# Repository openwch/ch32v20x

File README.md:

# 32-bit Enhanced Low-Power RISC-V MCU – CH32V203
EN | [中文](README_zh.md)

### Overview
The CH32V203 is an industrial-grade enhanced low-power general-purpose MCU based on 32-bit RISC-V core. The CH32V203 features high performance, and supports up to 144MHz system clock frequency. The operating power consumption can be as low as 45uA/MHz. CH32V203 integrates 2-channel USB interface which supports USB Host and USB Device functions. The CH32V203 provides 1-channel CAN interface (2.0B active), 2-channel OPA, 4 UARTs, 2 IICs, 12-bit ADC, 10-channel TouchKey and other peripheral resources. Several packages such as TSSOP20, QFN28 QFN48, LQFP32 and LQFP48 are available for users.

### System Block Diagram

### Features
- Qingke V4B, up to 144MHz system clock frequency;
- Single-cycle multiplication and hardware division;
- 20KB SRAM, 64KB Flash;
- Supply voltage: 2.5V/3.3V. GPIO unit is supplied independently;
- Low-power modes: sleep/stop/standby;
- Down to 44.65uA/MHz in Run mode;
- Down to 17.90uA/MHz in Sleep mode;
- Power-on/power-down reset (POR/PDR), programmable voltage detector (PVD);
- 1 x 18-channel general DMA controllers
- 2 amplifiers;
- 10-channel 12-bit ADC, 10-channel TouchKey;
- 4 timers;
- One USB2.0 full-speed host/device interface;
- One USB2.0 full-speed device interface
- 4 UARTs;
- One CAN interface (2.0B active);
- 2 IIC interfaces, 2 SPI interfaces;
- 37 I/O ports, can be mapped to 16 external interrupts;
- CRC calculation unit, 96-bit unique ID;
- Serial 2-wire debug interface;
- Packages: TSSOP20, QFN28, QFN48, LQFP32, LQFP48;

# 32-bit Wireless RISC-V MCU – CH32V208

### Overview
The CH32V208 is a wireless MCU based on 32-bit RISC-V core, with hardware stack area and fast interrupt entry. Compared with standard RISC-V, the interrupt response speed is greatly improved. The CH32V208 is based on V4C core. The memory protection unit is added and hardware division cycle is reduced. The CH32V208 integrates 2Mbps BLE communication module, 10M Ethernet module (MAC+PHY), USB2.0 full-speed device and host/device interface, CAN controller, etc.

### System Block Diagram

### Features
- Qingke V4C processor, up to 144MHz system clock frequency;
- Single-cycle multiplication and hardware division;
- 64KB SRAM, 128KB Flash;
- Supply voltage: 2.5V/3.3V. GPIO unit is supplied independently;
- Low-power modes: sleep/stop/standby;
- Bluetooth Low Energy 5.3;
- 10M Ethernet controller (MAC+PHY);
- Power-on/power-down reset (POR/PDR), programmable voltage detector (PVD);
- 2 amplifiers;
- 16-channel 12-bit ADC, 16-channel TouchKey;
- 5 timers;
- USB2.0 full-speed host/device + device interface;
- 4 USARTs;
- One CAN interface (2.0B active);
- 2 IIC interfaces, 2 SPI interfaces;
- 53 I/O ports, can be mapped to 16 external interrupts;
- CRC calculation unit, 96-bit unique ID;
- Serial 2-wire debug interface;
- Packages: LQFP64M, QFN68, QFN48, QFN28;

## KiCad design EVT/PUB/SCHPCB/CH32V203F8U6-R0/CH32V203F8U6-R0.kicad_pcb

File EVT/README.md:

# EVT

### -- download URL
*  CH32V20xEVT.ZIP-https://www.wch.cn/downloads/CH32V20xEVT_ZIP.html

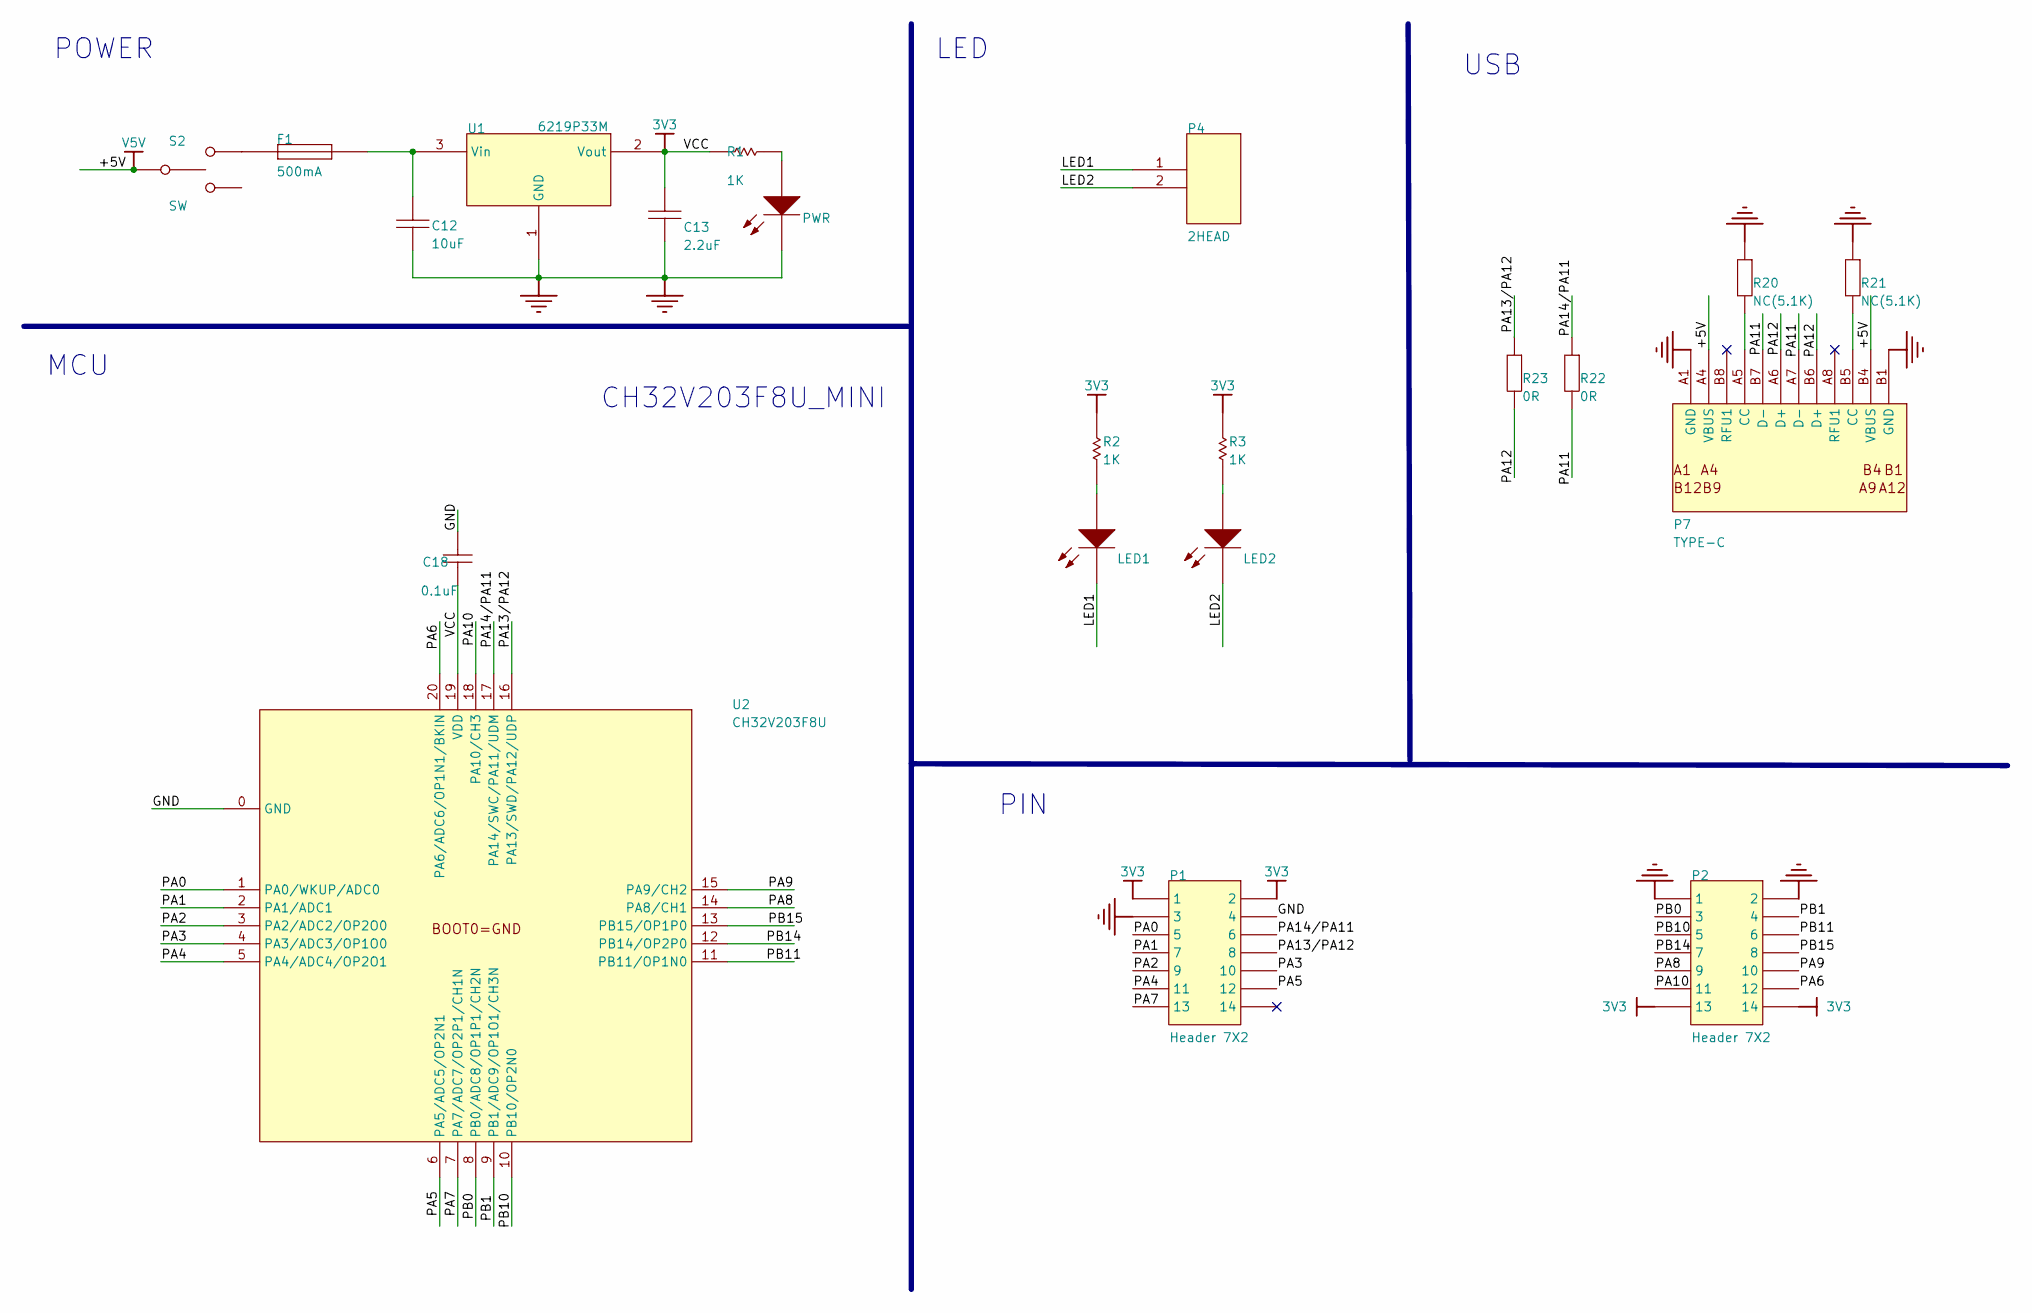
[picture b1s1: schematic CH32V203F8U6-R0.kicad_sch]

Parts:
C12: 10uF; 3216_C
C13: 2.2uF; 0603_C
C18: 0.1uF; 0603_C
F1: 500mA; 0603
LED1: LED1 blue; 0603+
LED2: LED2 blue; 0603+
P1, P2: Header 7X2; IDC14-2.54mm
P4: 2HEAD; SIP2-2.54mm
P7: TYPE-C; TYPE-C-Receptacle-2.0
PWR: POWER red; 0603+
R1, R2, R3: 1K; 0603
R20, R21: NC(5.1K); 0603
R22, R23: 0R; 0603
S2: SW; SW1
U1: 6219P33M; SOT-23
U2: CH32V203F8U; QFN20_3x3

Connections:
+5V: P7.A4 (VBUS), P7.B4 (VBUS), S2.1
LED1: LED1.2 (K), P4.1
LED2: LED2.2 (K), P4.2
NetC12_1: C12.1, F1.2, U1.3 (Vin)
NetF1_1: F1.1, S2.3
NetLED1_1: LED1.1 (A), R2.2
NetLED2_1: LED2.1 (A), R3.2
NetP7_A5: P7.A5 (CC), R20.1
NetP7_B5: P7.B5 (CC), R21.1
NetPWR_1: PWR.1 (A), R1.1
PA0: P1.5, U2.1 (PA0/WKUP/ADC0)
PA1: P1.7, U2.2 (PA1/ADC1)
PA2: P1.9, U2.3 (PA2/ADC2/OP2O0)
PA3: P1.10, U2.4 (PA3/ADC3/OP1O0)
PA4: P1.11, U2.5 (PA4/ADC4/OP2O1)
PA5: P1.12, U2.6 (PA5/ADC5/OP2N1)
PA6: P2.12, U2.20 (PA6/ADC6/OP1N1/BKIN)
PA7: P1.13, U2.7 (PA7/ADC7/OP2P1/CH1N)
PA8: P2.9, U2.14 (PA8/CH1)
PA9: P2.10, U2.15 (PA9/CH2)
PA10: P2.11, U2.18 (PA10/CH3)
PA11: P7.A7 (D-), P7.B7 (D-), R22.1
PA12: P7.A6 (D+), P7.B6 (D+), R23.1
PA13/PA12: P1.8, R23.2, U2.16 (PA13/SWD/PA12/UDP)
PA14/PA11: P1.6, R22.2, U2.17 (PA14/SWC/PA11/UDM)
PB0: P2.3, U2.8 (PB0/ADC8/OP1P1/CH2N)
PB1: P2.4, U2.9 (PB1/ADC9/OP1O1/CH3N)
PB10: P2.5, U2.10 (PB10/OP2N0)
PB11: P2.6, U2.11 (PB11/OP1N0)
PB14: P2.7, U2.12 (PB14/OP2P0)
PB15: P2.8, U2.13 (PB15/OP1P0)
VCC: C13.2, C18.1, P1.1, P1.2, P2.13, P2.14, R1.2, R2.1, R3.1, U1.2 (Vout), U2.19 (VDD)

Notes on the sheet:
PIN
LED
POWER
CH32V203F8U_MINI
MCU
USB

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
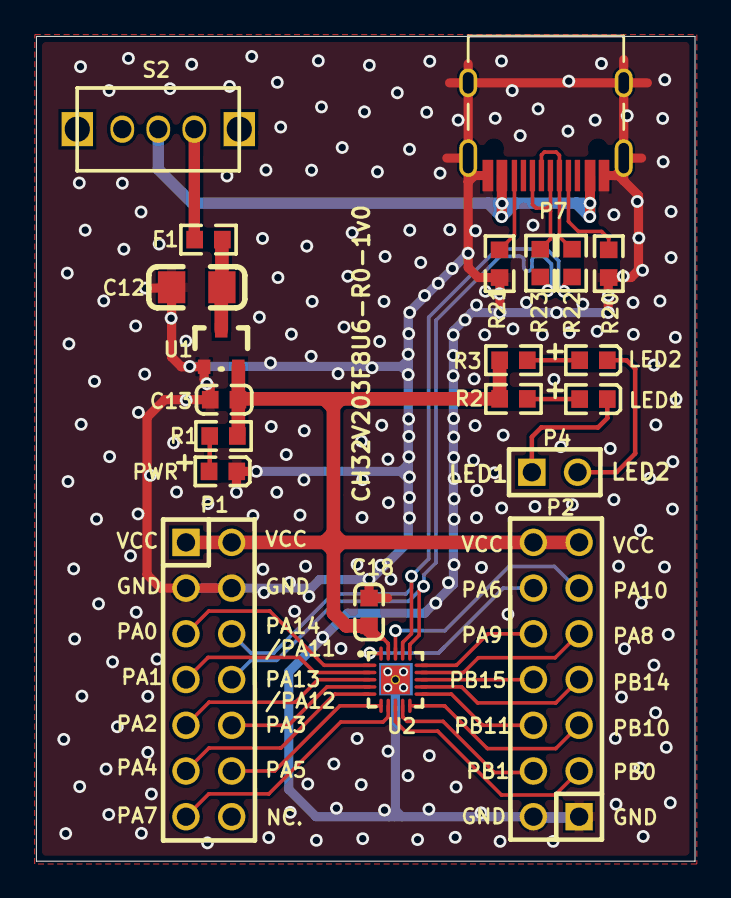
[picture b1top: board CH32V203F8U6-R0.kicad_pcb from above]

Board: 2 copper layers, 36.6 x 45.8 mm, 21 parts (0 on the bottom side), 33 nets.

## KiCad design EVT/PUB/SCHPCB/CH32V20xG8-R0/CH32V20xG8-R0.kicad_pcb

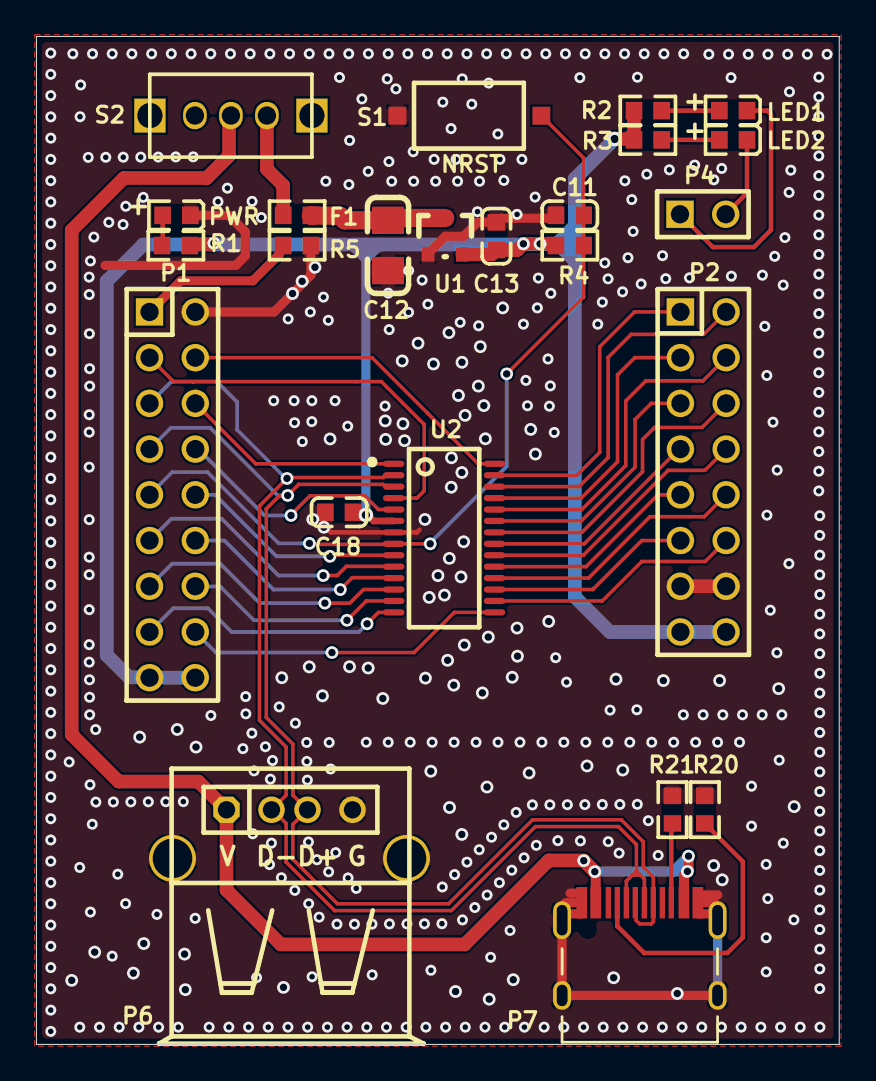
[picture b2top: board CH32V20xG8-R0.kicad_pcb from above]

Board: 2 copper layers, 44.6 x 56.0 mm, 24 parts (0 on the bottom side), 39 nets.

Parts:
C11, C18: 0.1uF; 0603_C
C12: 10uF; 3216_C
C13: 2.2uF; 0603_C
F1: 500mA; 0603
LED1: LED1 blue; 0603+
LED2: LED2 blue; 0603+
P1: HEADER 9x2; IDC18-2.54MM
P2: Header 8X2; IDC16-2.54mm
P4: 2HEAD; SIP2-2.54mm
P6: USB_A; USBAF
P7: TYPE-C; TYPE-C-Receptacle-2.0
PWR: POWER red; 0603+
R1, R2, R3: 1K; 0603
R4, R5: 10K; 0603
R20, R21: NC(5.1K); 0603
S1: NRST; SMD_6.1x3.65x2.5mm-KEY
S2: SW; KEY2
U1: 6219P33M; SOT-23
U2: CH32V203G8R; QSOP28

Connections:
+5V: P6.1, P7.A4, P7.B4, S2.1
BOOT0: P1.3, U2.4
GND: C11.1, C12.2, C13.1, C18.1, P1.2, P2.13, P2.14, P6.0, P6.4, P7.0, P7.A1, P7.B1, PWR.2, R5.1, R20.2, R21.2, S1.2, U1.1, U2.7
LED1: LED1.2, P4.1
LED2: LED2.2, P4.2
NRST: C11.2, P1.9, R4.1, S1.1, U2.8
NetC12_1: C12.1, F1.2, U1.3
NetF1_1: F1.1, S2.3
NetLED1_1: LED1.1, R2.2
NetLED2_1: LED2.1, R3.2
NetP1_1: P1.1, R5.2
NetP7_A5: P7.A5, R20.1
NetP7_B5: P7.B5, R21.1
NetPWR_1: PWR.1, R1.1
PA0: P1.10, U2.9
PA1: P1.11, U2.10
PA2: P1.12, U2.11
PA3: P1.13, U2.12
PA4: P1.16, U2.15
PA5: P2.12, U2.16
PA6: P1.14, U2.13
PA7: P2.11, U2.17
PA8: P2.4, U2.24
PA9: P2.3, U2.25
PA10: P2.2, U2.26
PA11: P2.1, U2.27
PA12: P1.4, U2.28
PA14: P1.6, U2.1
PB0: P1.15, U2.14
PB1: P2.8, U2.20
PB6: P1.5, P6.2, P7.A7, P7.B7, U2.2
PB7: P1.7, P6.3, P7.A6, P7.B6, U2.3
PB8: P1.8, U2.5
PB10: P2.10, U2.18
PB11: P2.9, U2.19
PB13: P2.7, U2.21
PB14: P2.6, U2.22
PB15: P2.5, U2.23
VCC: C13.2, C18.2, P1.17, P1.18, P2.15, P2.16, R1.2, R2.1, R3.1, R4.2, U1.2, U2.6

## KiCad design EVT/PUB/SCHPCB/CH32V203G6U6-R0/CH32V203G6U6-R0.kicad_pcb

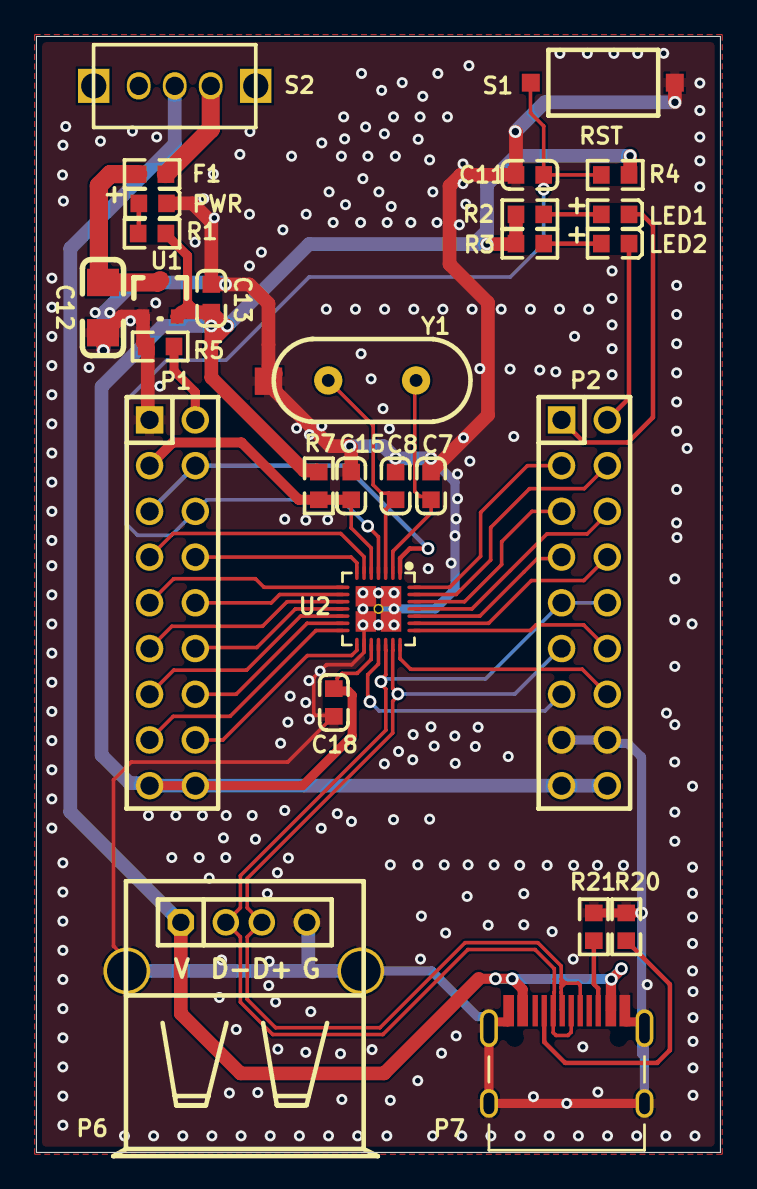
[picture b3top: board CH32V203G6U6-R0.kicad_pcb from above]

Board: 2 copper layers, 38.0 x 62.0 mm, 28 parts (0 on the bottom side), 39 nets.

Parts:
C7, C8: 22pF; 0603_C
C11, C15, C18: 0.1uF; 0603_C
C12: 10uF; 3216_C
C13: 2.2uF; 0603_C
F1: 500mA; 0603
LED1: LED1 blue; 0603+
LED2: LED2 blue; 0603+
P1, P2: HEADER 9x2; IDC18-2.54MM
P6: USB_A; USBAF
P7: TYPE-C; TYPE-C-Receptacle-2.0
PWR: POWER red; 0603+
R1, R2, R3: 1K; 0603
R4: NC(10K); 0603
R5: 4.7K; 0603
R7: 0Ω; 0603
R20, R21: NC(5.1K); 0603
S1: RST; SMD_6.1x3.65x2.5mm-KEY
S2: SW; KEY2
U1: 6219P33M; SOT-23
U2: CH32V203G6U; QFN28_4x4
Y1: 8M; XT_AT49

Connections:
+5V: P6.1, P7.A4, P7.B4, S2.1
BOOT0: P1.4, P1.5, U2.1
GND: C7.1, C8.1, C11.1, C12.2, C13.1, C15.2, C18.1, P1.1, P2.15, P2.16, P6.0, P6.4, P7.0, P7.A1, P7.B1, PWR.2, R5.2, R20.2, R21.2, S1.2, U1.1, U2.0, U2.16, Y1.0
LED1: LED1.2, P2.1
LED2: LED2.2, P2.2
NRST: C11.2, P1.6, R4.1, S1.1, U2.4
NetC12_1: C12.1, F1.2, U1.3
NetF1_1: F1.1, S2.3
NetLED1_1: LED1.1, R2.2
NetLED2_1: LED2.1, R3.2
NetP1_2: P1.2, R5.1
NetP7_A5: P7.A5, R20.1
NetP7_B5: P7.B5, R21.1
NetPWR_1: PWR.1, R1.1
PA0: P1.7, U2.6
PA1: P1.8, U2.7
PA2: P1.9, U2.8
PA3: P1.10, U2.9
PA4: P1.11, U2.10
PA5: P1.12, U2.11
PA6: P1.13, U2.12
PA7: P1.14, U2.13
PA9: P2.13, U2.18
PA10: P2.9, P2.10, P6.2, P7.A7, P7.B7, U2.19
PA12: P2.11, P6.3, P7.A6, P7.B6, U2.20
PA13: P2.14, U2.21
PA14: P2.12, U2.22
PA15: P2.8, U2.23
PB0: P1.15, U2.14
PB1: P1.16, U2.15
PB3: P2.7, U2.24
PB4: P2.6, U2.25
PB5: P2.5, U2.26
PB6: P2.4, U2.27
PB7: P2.3, U2.28
PD0: C7.2, U2.2, Y1.2
PD1: C8.2, U2.3, Y1.1
VCC: C13.2, C18.2, P1.17, P1.18, P2.17, P2.18, R1.2, R2.1, R3.1, R4.2, R7.1, U1.2, U2.17
VDDA: C15.1, P1.3, R7.2, U2.5

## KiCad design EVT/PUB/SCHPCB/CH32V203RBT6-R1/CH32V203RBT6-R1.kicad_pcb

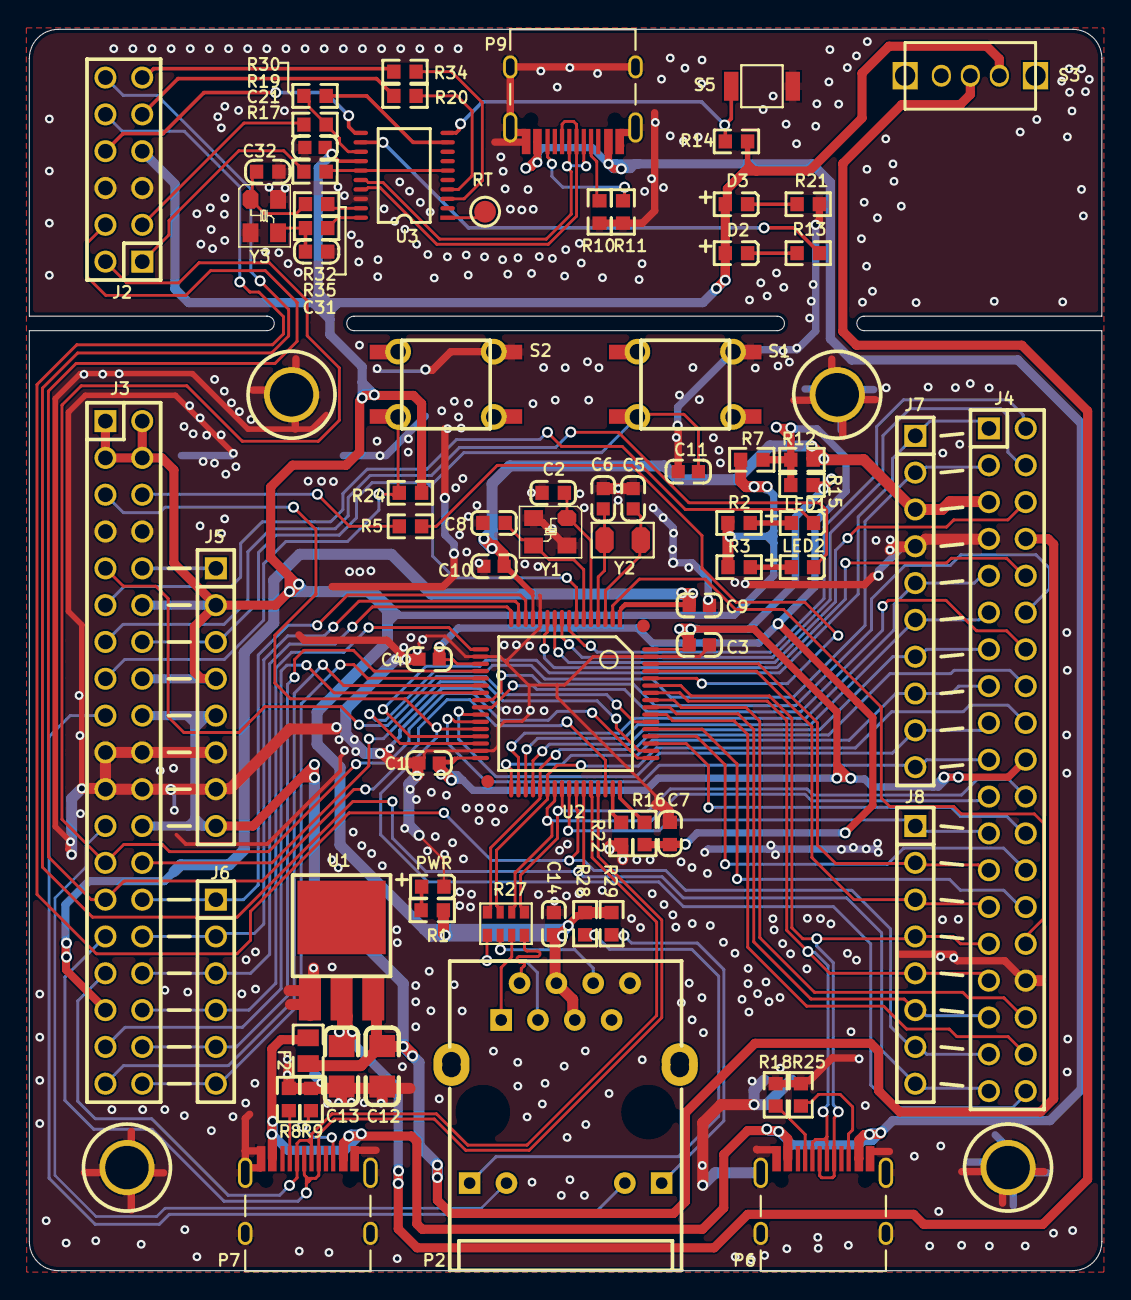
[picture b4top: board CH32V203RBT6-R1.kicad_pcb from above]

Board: 2 copper layers, 74.0 x 85.6 mm, 74 parts (0 on the bottom side), 107 nets.

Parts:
C1, C3, C4, C7, C9, C10, C11, C21: 0.1uF; 0603_C
C2, C8: 22pF; 0603_C
C5, C6: 12pF; 0603_C
C12, C13: 10uF; 3216_C
C14: 1uF; 0603_C
C31, C32: NC(22pF); 0603_C
D2: BLUE; 0603+
D3: RED; 0603+
F2: 500mA; 0805
J2: Header 6X2; IDC12-2.54mm
J3, J4: Header 19X2; IDC38-2.54mm
J5, J8: Header 8; SIP8-2.54mm
J6: Header 6; SIP6-2.54MM
J7: Header 10; SIP10-2.54mm
LED1: LED1 blue; 0603+
LED2: LED2 blue; 0603+
P2: HR911105A
P6, P9: TYPE-C; TYPE-C-Receptacle-2.0
P7: USBFS; TYPE-C-Receptacle-2.0
PWR: POWER red; 0603+
R1, R2, R3, R13, R21, R28, R29, R30: 1K; 0603
R5, R14, R24: 10K; 0603
R7, R12, R15: 0Ω; 0603
R8, R9, R10, R11, R18, R25: NC(5.1K); 0603
R16, R22: 0; 0603
R17, R19: 100; 0603
R20, R34: 270; 0603
R27: 0Ω; 8P4R-0603
R32, R35: NC(0R); 0603
RT: Testpoint; TESTPOINT1
S1: RESET; KEYX
S2: USER; KEYX
S3: SW; SW1
S5: KEY; 贴片按键
U1: 1117-3.3V; SOT-223
U2: CH32V307R; LQFP64M_10X10
U3: CH32V305F; TSSOP20
Y1: 8MHz; XT3225
Y2: 32.768k; FC-135
Y3: NC(12M); XT3225

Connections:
5V_in: F2.1, P6.A4, P6.B4, P7.A4, P7.B4, P9.A4, P9.B4
+5V: C12.1, F2.2, J3.18, J3.24, J4.8, J5.5, J5.8, U1.3
BOOT0: R5.2, U2.60
BOOT1: J3.5, J4.38, U2.28
CLK: J2.2, J3.25, U2.49
CLK0: J2.1, R17.1
DIO: J2.4, J3.27, U2.46
DIO0: J2.3, R19.1
D_SWCLK: R17.2, U3.6, U3.15
D_SWDIO: R19.2, R30.1, U3.13
ELED1: J3.23, P2.10
ELED2: J3.17, P2.11
ERXN: J4.18, R27.3, U2.38
ERXN1: P2.6, R27.6
ERXP: J4.16, R27.4, U2.37
ERXP1: P2.3, R27.5
ETXN: J4.22, R27.1, U2.40
ETXN1: P2.2, R27.8
ETXP: J4.21, R27.2, U2.39
ETXP1: P2.1, R27.7
GND: C1.1, C2.1, C3.1, C4.1, C5.2, C6.2, C7.1, C8.1, C9.2, C10.2, C11.1, C12.2, C13.2, C14.1, C21.2, C31.1, C32.1, J2.5, J2.6, J3.7, J3.8, J3.19, J3.20, J3.21, J3.22, J4.7, J4.32, J5.6, J5.7, J7.4, P2.8, P6.0, P6.A1, P6.B1, P7.0, P7.A1, P7.B1, P9.0, P9.A1, P9.B1, PWR.2, R8.1, R9.1, R10.2, R11.2, R18.1, R21.1, R22.1, R25.1, S1.3, S2.3, S5.2, U1.1, U2.12, U2.18, U2.31, U2.63, U3.18, Y1.2, Y1.4, Y3.2, Y3.4
IAP: R14.1, S5.1, U3.10
KEY: J3.15, R24.1, S2.1
LED1: J3.11, LED1.2
LED2: J3.13, LED2.2
LED_CON: R13.1, U3.12
NRST: C11.2, J3.14, J5.3, S1.1, U2.7
NetC13_1: C13.1, S3.1, U1.2
NetD2_2: D2.2, R13.2
NetD3_2: D3.2, R21.2
NetJ3_6: J3.6, R5.1
NetJ3_10: J3.10, J5.1
NetLED1_1: LED1.1, R2.2
NetLED2_1: LED2.1, R3.2
NetP2_9: P2.9, R28.2
NetP2_12: P2.12, R29.2
NetP6_A5: P6.A5, R18.2
NetP6_B5: P6.B5, R25.2
NetP7_A5: P7.A5, R8.2
NetP7_B5: P7.B5, R9.2
NetP9_A5: P9.A5, R10.1
NetP9_B5: P9.B5, R11.1
NetPWR_1: PWR.1, R1.1
NetR16_2: R16.2, U2.48
NetR22_2: R22.2, U2.47
OSC_IN: C32.2, R32.2, Y3.1
OSC_OUT: C31.2, R35.2, Y3.3
PA0: J3.28, J6.1, U2.14
PA1: J3.30, J6.2, U2.15
PA2: J3.32, J6.3, U2.16
PA3: J3.34, J6.4, U2.17
PA4: J3.36, J6.5, U2.20
PA5: J3.38, J6.6, U2.21
PA6: J3.37, U2.22
PA7: J3.35, U2.23
PA8: J4.23, J8.1, U2.41
PA9: J2.10, J4.35, J8.7, U2.42
PA10: J2.12, J4.37, J8.8, U2.43
PA11: J3.31, P7.A7, P7.B7, U2.44
PA12: J3.29, P7.A6, P7.B6, U2.45
PA15: J3.26, U2.50
PB0: J4.17, J7.9, U2.26
PB1: J4.19, J7.10, U2.27
PB3: J4.36, U2.55
PB4: J4.33, J8.6, U2.56
PB5: J4.34, U2.57
PB6: J4.31, J8.5, P6.A7, P6.B7, U2.58
PB7: J4.29, J8.4, P6.A6, P6.B6, U2.59
PB8: J4.27, J8.3, U2.61
PB9: J4.25, J8.2, U2.62
PB10: J4.1, J7.1, U2.29
PB11: J4.3, J7.2, U2.30
PB12: J4.15, J7.8, U2.33
PB13: J4.9, J7.5, U2.34
PB14: J4.11, J7.6, U2.35
PB15: J4.13, J7.7, U2.36
PC0: J4.2, U2.8
PC1: J4.4, U2.9
PC2: J4.6, U2.10
PC3: J4.10, U2.11
PC4: J4.12, U2.24
PC5: J4.14, U2.25
PC6_305: R30.2, U3.9
PC10: J4.24, U2.51
PC11: J4.26, U2.52
PC12: J4.28, U2.53
PC13: J4.30, U2.2
PC14: C5.1, U2.3, Y2.1
PC15: C6.1, U2.4, Y2.2
PD0: C2.2, U2.5, Y1.1
PD0_305: R32.1, U3.19
PD1: C8.2, U2.6, Y1.3
PD1_305: R35.1, U3.20
PD2: J3.9, U2.54
RST0: J2.8, U3.11
RT: RT.1, U3.1
RX_OUT: J2.9, R20.1
TX_OUT: J2.11, R34.1
UART3_RX: R20.2, U3.4
UART3_TX: R34.2, U3.3
USB_N: P9.A7, P9.B7, U3.16
USB_P: P9.A6, P9.B6, U3.17
VBAT: C9.1, J3.33, U2.1
VCC: C14.2, C21.1, D2.1, D3.1, J2.7, J3.1, J3.2, J3.3, J3.4, J3.12, J3.16, J5.2, J5.4, P2.4, P2.5, R1.2, R2.1, R3.1, R7.1, R14.2, R24.2, R28.1, R29.1, S3.3, U3.14
VDD: C4.2, C7.2, R7.2, R12.2, R15.2, R16.1, U2.19
VDDA: C10.1, J4.5, J7.3, R12.1, U2.13
VIO: C1.2, C3.2, J4.20, R15.1, U2.32, U2.64

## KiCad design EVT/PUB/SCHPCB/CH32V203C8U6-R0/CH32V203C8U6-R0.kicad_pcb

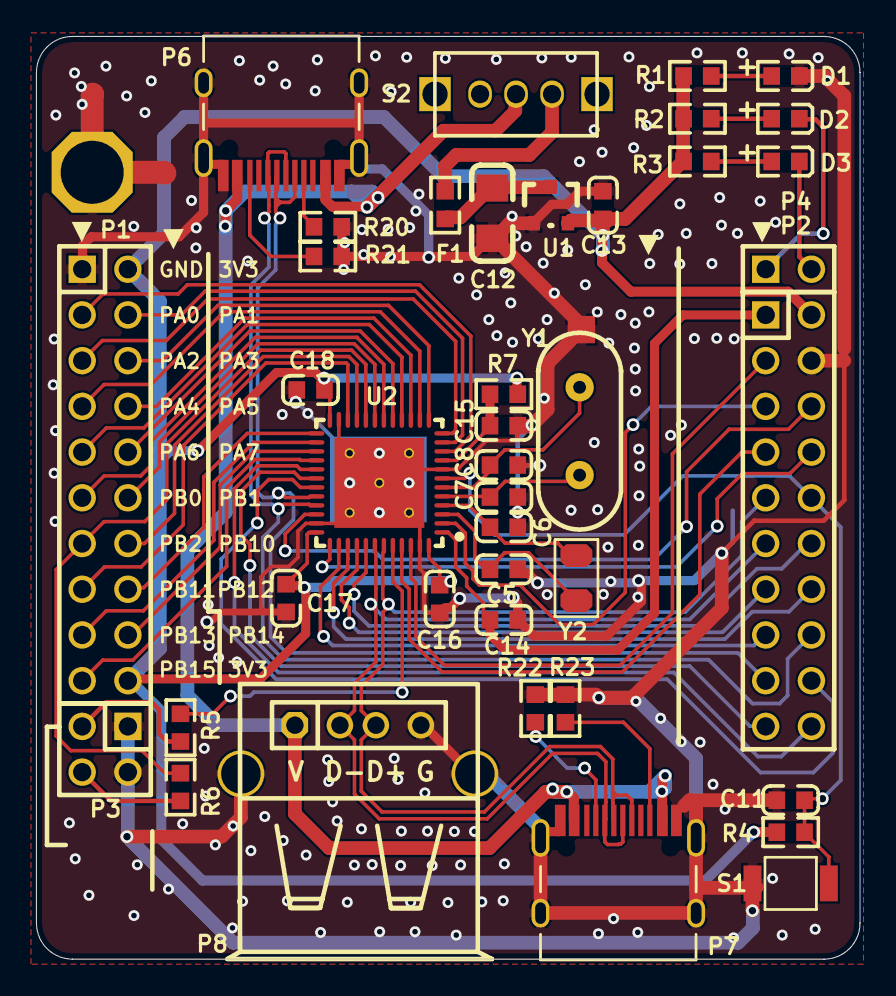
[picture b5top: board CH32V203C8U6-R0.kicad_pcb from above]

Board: 2 copper layers, 45.8 x 51.3 mm, 40 parts (0 on the bottom side), 57 nets.

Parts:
C5, C6: 12pF; 0603_C
C7, C8: 22pF; 0603_C
C11, C14, C15, C16, C17, C18: 0.1uF; 0603_C
C12: 10uF; 3216_C
C13: 10uF; 0603_C
D1: POWER red; 0603+
D2: LED1; 0603+
D3: LED2; 0603+
F1: 500mA; 0603
P1, P2: HEADER 10x2; IDC20-2.54MM
P3: Header 2X2; IDC4-2.54mm
P4: HEADER 2; SIP2-2.54mm
P6, P7: TYPE-C; TYPE-C-Receptacle-2.0
P8: USB_A; USBAF
R1, R2, R3: 1K; 0603
R4, R5, R6: 10K; 0603
R7: 0Ω; 0603
R20, R21, R22, R23: NC(5.1K); 0603
S1: RST; 贴片按键
S2: SW; KEY2
U1: 6219P33M; SOT-23
U2: CH32V203CxU; QFN48_7X7
Y1: 8M; XT_AT49
Y2: 32.768k; FC-135

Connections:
+5V: P6.A4, P6.B4, P7.A4, P7.B4, P8.1, S2.1
BOOT0: R5.1, U2.44
BOOT1: P1.13, R6.1, U2.20
GND: C5.2, C6.2, C7.1, C8.1, C11.1, C12.2, C13.2, C14.2, C15.2, C16.1, C17.1, C18.1, D1.2, P1.1, P2.4, P3.1, P3.2, P6.0, P6.A1, P6.B1, P7.0, P7.A1, P7.B1, P8.0, P8.4, R20.2, R21.2, R22.2, R23.2, S1.2, U1.1, U2.0, U2.8, U2.23, U2.35, U2.47, Y1.0
LED1: D2.2, P4.1
LED2: D3.2, P4.2
NRST: C11.2, P2.10, R4.1, S1.1, U2.7
NetD1_1: D1.1, R1.1
NetD2_1: D2.1, R2.2
NetD3_1: D3.1, R3.2
NetF1_1: F1.1, S2.3
NetP3_3: P3.3, R5.2
NetP3_4: P3.4, R6.2
NetP6_A5: P6.A5, R20.1
NetP6_B5: P6.B5, R21.1
NetP7_A5: P7.A5, R22.1
NetP7_B5: P7.B5, R23.1
PA0: P1.3, U2.10
PA1: P1.4, U2.11
PA2: P1.5, U2.12
PA3: P1.6, U2.13
PA4: P1.7, U2.14
PA5: P1.8, U2.15
PA6: P1.9, U2.16
PA7: P1.10, U2.17
PA8: P2.20, U2.29
PA9: P2.19, U2.30
PA10: P2.18, U2.31
PA11: P2.17, P6.A7, P6.B7, U2.32
PA12: P2.16, P6.A6, P6.B6, U2.33
PA13: P2.6, U2.34
PA14: P2.8, U2.37
PA15: P2.15, U2.38
PB0: P1.11, U2.18
PB1: P1.12, U2.19
PB3: P2.14, U2.39
PB4: P2.13, U2.40
PB5: P2.12, U2.41
PB6: P2.11, P7.A7, P7.B7, P8.2, U2.42
PB7: P2.9, P7.A6, P7.B6, P8.3, U2.43
PB8: P2.7, U2.45
PB9: P2.3, U2.46
PB10: P1.14, U2.21
PB11: P1.15, U2.22
PB12: P1.16, U2.25
PB13: P1.17, U2.26
PB14: P1.18, U2.27
PB15: P1.19, U2.28
PC13: P2.5, U2.2
PC14: C5.1, U2.3, Y2.1
PC15: C6.1, U2.4, Y2.2
PD0: C7.2, U2.5, Y1.2
PD1: C8.2, U2.6, Y1.1
V5V: C12.1, F1.2, U1.3
VBAT: C14.1, P2.1, U2.1
VCC: C13.1, C16.2, C17.2, C18.2, P1.2, P1.20, P2.2, R1.2, R2.1, R3.1, R4.2, R7.1, U1.2, U2.24, U2.36, U2.48
VDDA: C15.1, R7.2, U2.9

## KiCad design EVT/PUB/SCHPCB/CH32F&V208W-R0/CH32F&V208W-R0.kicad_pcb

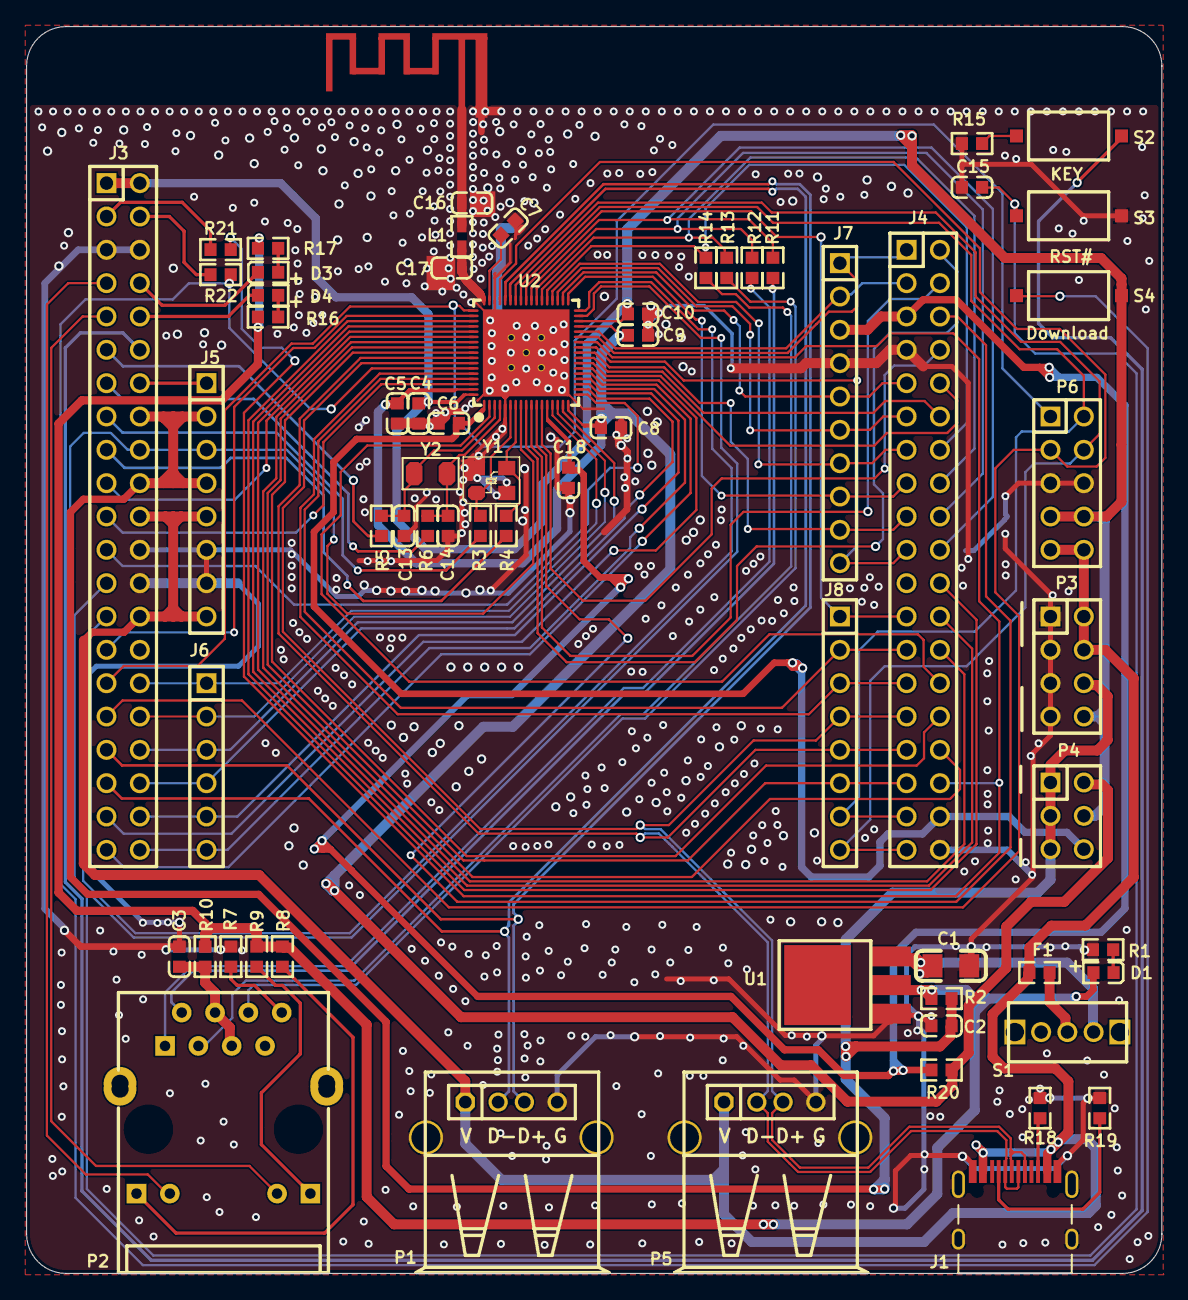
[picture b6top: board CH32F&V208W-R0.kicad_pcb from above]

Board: 2 copper layers, 86.5 x 95.0 mm, 65 parts (0 on the bottom side), 96 nets.

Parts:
C1: 10uF; 3216_C
C2: 10uF; 0603_C
C3, C7: 1uF; 0603_C
C4, C5, C6, C8, C9, C10, C15, C18: 0.1uF; 0603_C
C13, C14: 12pF; 0603_C
C16: 1.5pF; 0603_C
C17: 1pF; 0603_C
D1: power; 0603+
D3, D4: RED; 0603+
E1: ANTENNA; ANT-F-1-2.4G-1.6
F1: 500mA; 0603
J1: TYPE-C-Receptacle-2.0
J3: Header 21X2; IDC42-2.54mm
J4: Header 19X2; IDC38-2.54mm
J5, J8: Header 8; SIP8-2.54mm
J6: Header 6; SIP6-2.54MM
J7: Header 10; SIP10-2.54mm
L1: 1.8nH; 0603
P1, P5: USB; USBAF
P2: HR911105A
P3: HEADER 4x2; IDC8-2.54mm
P4: Psel; IDC6-2.54mm
P6: LINK; IDC10-2.54mm
R1, R8, R9, R16, R17: 1K; 0603
R2, R7, R10, R20: 0Ω; 0603
R3, R4, R5, R6, R11, R12, R13, R14: NC(0R); 0603
R15, R21, R22: 10K; 0603
R18, R19: NC(5.1K); 0603
S1: SW SPDT; KEY_B
S2: KEY; SMD_6.1x3.65x2.5mm-KEY
S3: RST#; SMD_6.1x3.65x2.5mm-KEY
S4: Download; SMD_6.1x3.65x2.5mm-KEY
U1: 1117-3.3V; SOT-223
U2: CH32V208W; QFN68_8x8
Y1: 32MHz; XT3225
Y2: 32768Hz; FC-135

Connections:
3V3: C2.1, J3.16, J3.20, J5.2, J5.4, P3.6, P4.1, P4.3, P4.5, R2.1
3V3S: D1.1, R2.2, R8.1, R9.1, R10.2, R16.1, R17.1, U1.2
+5V: F1.1, J1.A4, J1.B4, J3.22, J3.28, J5.5, J5.8, P1.1, P3.2, P3.4, P5.1, P6.9, P6.10
ANT: C17.2, L1.1, U2.51
BOOT0: R22.2, S4.2, U2.63
BOOT1: J4.34, R21.1, U2.28
CC1: J1.A5, R19.1
CC2: J1.B5, R18.1
ELED1: J3.7, P2.10
ELED2: J3.9, P2.11
ERXN: P2.6, R13.2
ERXP: P2.3, R14.2
ETXN: P2.2, R11.2
ETXP: P2.1, R12.2
GND: C1.2, C2.2, C3.1, C4.2, C5.1, C6.2, C7.2, C8.2, C9.2, C10.1, C13.1, C14.1, C15.1, C16.1, C17.1, C18.2, E1.0, J1.0, J1.A1, J1.B1, J3.5, J3.6, J3.24, J3.26, J4.7, J4.38, J5.6, J5.7, J7.4, P1.0, P1.4, P3.1, P3.3, P3.5, P3.7, P5.0, P5.4, P6.5, P6.6, R1.1, R7.1, R15.1, R18.2, R19.2, S3.1, U1.1, U2.0, U2.5, U2.49, Y1.2, Y1.4
KEY: J3.12, S2.1
LED1: D3.2, J3.8
LED2: D4.2, J3.10
NRST: C15.2, J3.18, J5.3, S3.2, U2.8
NetC3_2: C3.2, P2.4, P2.5, R10.1
NetC16_2: C16.2, E1.1, L1.2
NetD1_2: D1.2, R1.2
NetD3_1: D3.1, R17.2
NetD4_1: D4.1, R16.2
NetF1_2: F1.2, S1.1
NetJ3_3: J3.3, R21.2
NetJ3_4: J3.4, R22.1
NetJ3_14: J3.14, J5.1
NetP2_8: P2.8, R7.2
NetP2_9: P2.9, R8.2
NetP2_12: P2.12, R9.2
NetR15_2: R15.2, S2.2
PA0: J3.32, J6.1, U2.14
PA1: J3.34, J6.2, U2.15
PA2: J3.36, J6.3, U2.16
PA3: J3.38, J6.4, U2.19
PA4: J3.40, J6.5, U2.20
PA5: J3.42, J6.6, U2.21
PA6: J3.41, U2.22
PA7: J3.39, U2.23
PA8: J4.23, J8.1, U2.43
PA9: J4.35, J8.7, P6.2, U2.44
PA10: J4.37, J8.8, P6.4, U2.45
PA11: J3.37, P1.2, U2.46
PA12: J3.35, P1.3, U2.47
PA13: J3.33, P6.3, U2.48
PA14: J3.31, P6.1, U2.52
PA15: J3.29, U2.53
PB0: J4.17, J7.9, U2.26
PB1: J4.19, J7.10, U2.27
PB3: J4.32, U2.58
PB4: J4.33, J8.6, U2.59
PB5: J4.30, U2.60
PB6: J1.A7, J1.B7, J4.31, J8.5, P5.2, U2.61
PB7: J1.A6, J1.B6, J4.29, J8.4, P5.3, U2.62
PB8: J4.27, J8.3, U2.64
PB9: J4.25, J8.2, U2.65
PB10: J4.1, J7.1, U2.29
PB11: J4.3, J7.2, U2.30
PB12: J4.15, J7.8, U2.35
PB13: J4.9, J7.5, U2.36
PB14: J4.11, J7.6, U2.37
PB15: J4.13, J7.7, U2.38
PC0: J4.2, U2.9
PC1: J4.4, U2.10
PC2: J4.6, U2.11
PC3: J4.8, U2.12
PC4: J4.10, U2.24
PC5: J4.12, U2.25
PC6: J4.14, R14.1, U2.39
PC7: J4.16, R13.1, U2.40
PC8: J4.18, R12.1, U2.41
PC9: J4.20, R11.1, U2.42
PC10: J4.22, U2.54
PC11: J4.24, U2.55
PC12: J4.26, U2.56
PC13: J4.28, U2.2
PC14: J3.11, R5.1
PC15: J3.13, R6.1
PD0: J3.15, R3.1
PD1: J3.17, R4.1
PD2: J3.19, U2.57
PD3: J3.21, U2.66
PD4: J3.23, U2.18
PD5: J3.25, U2.33
PD6: J3.27, U2.34
V5V: C1.1, S1.2, U1.3
VBAT: C6.1, J4.36, P4.6, U2.1
VDD: C4.1, C10.2, J3.1, J3.2, P3.8, P4.4, P6.7, P6.8, S4.1, U2.32, U2.68
VDDA: C18.1, J4.5, J7.3, R20.2, U2.13
VINTA: C7.1, U2.50
VIO: C5.2, C8.1, C9.1, P4.2, R20.1, U2.17, U2.31, U2.67
X32IN: C13.2, R5.2, U2.3, Y2.1
X32OUT: C14.2, R6.2, U2.4, Y2.2
XIN: R3.2, U2.6, Y1.1
XOUT: R4.2, U2.7, Y1.3

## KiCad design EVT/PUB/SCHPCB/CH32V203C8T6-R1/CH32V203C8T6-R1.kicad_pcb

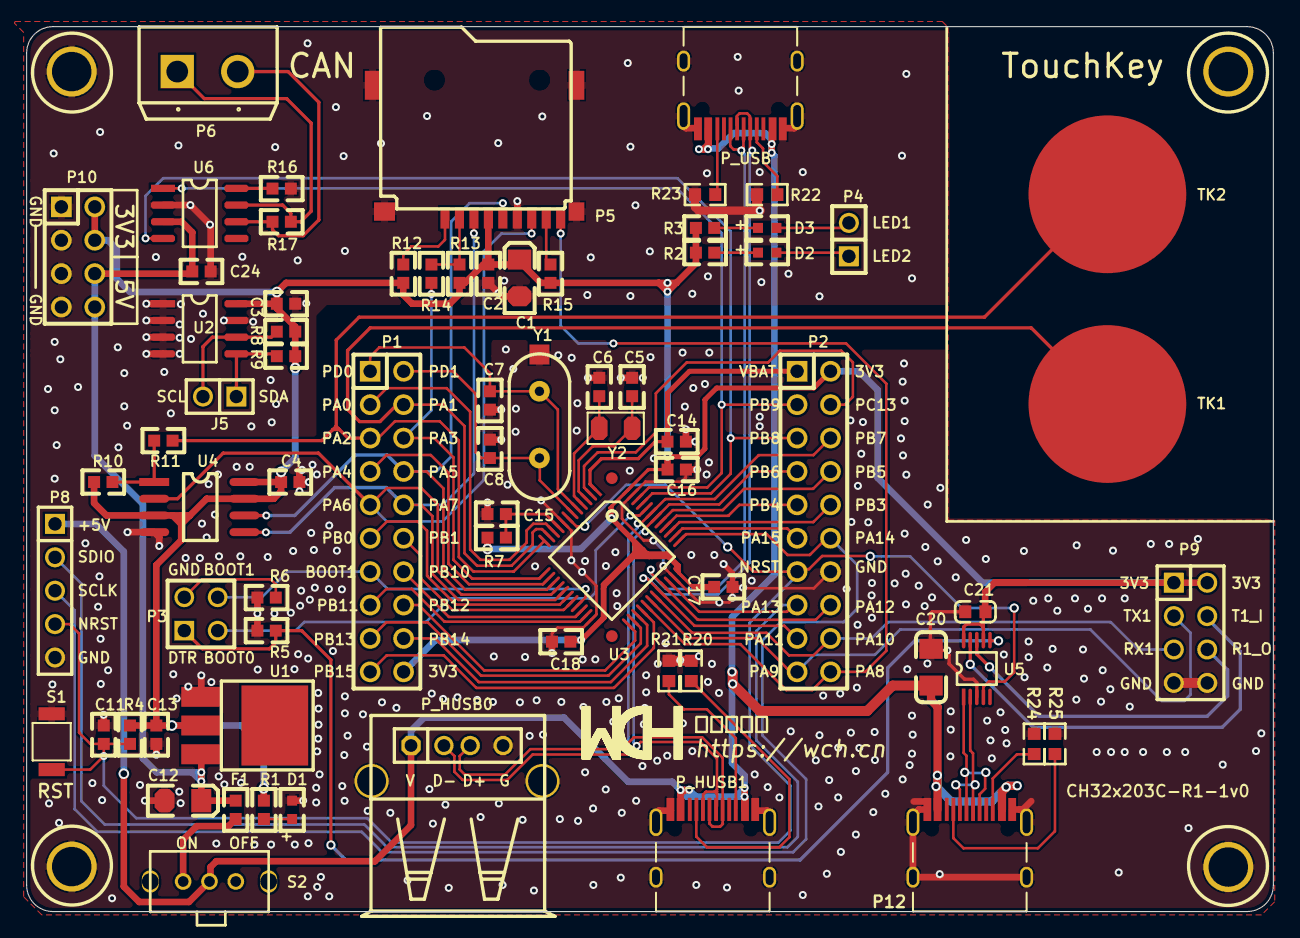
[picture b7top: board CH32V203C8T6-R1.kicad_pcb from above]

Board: 2 copper layers, 94.8 x 67.3 mm, 72 parts (0 on the bottom side), 72 nets.

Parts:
C1: NC(10uF); 3216
C2, C4, C11, C14, C15, C16, C17, C18: 0.1uF; 0603
C3, C24: NC(0.1uF); 0603
C5, C6: 12pF; 0603
C7, C8: 22pF; 0603
C12: 10uF; 3216
C13: 10uF; 0603
C20: NC(10uF); 3216_C
C21: NC(0.1uF); 0603_C
D1: POWER; 0603L
D2: LED1 blue; 0603L
D3: LED2 blue; 0603L
F1: 500mA; 0603
J5: Header 2; SIP2 - 40mil
P1, P2: Header 10X2; IDC20
P3: Header 2X2; HDR2X2
P4: Header 2; SIP2 - 40mil
P5: TF_自弹; TF_CARD
P6: Header 2; PORT2 4.5MM
P8: Header 5; SIP5 - 40mil
P9: HEADER 4x2; IDC8-2.54mm
P10: Header 4X2; IDC8
P12: TYPE-C; TYPE-C-Receptacle-2.0
P_HUSB0: USB_A; USBA-l
P_HUSB1: TYPE-C; TYPE-C-Receptacle-2.0
P_USB: TYPE-C; TYPE-C-Receptacle-2.0
R1, R2, R3: 1K; 0603
R4, R5, R6, R10: 10K; 0603
R7: 0Ω; 0603
R8, R9, R12, R13, R15: NC(10K); 0603
R11, R14, R16: NC(0Ω); 0603
R17: NC(120Ω); 0603
R20, R21, R22, R23, R24, R25: NC(5.1K); 0603
S1: KEY; 贴片按键
S2: SW; KEY2
TK1: KEY6; KEY68
TK2: KEY7; KEY68
U1: 1117-3.3V; SOT-223
U2: NC(24C02); SOP8
U3: CH32V203CxT; LQFP48
U4: W25Q16; 016 SO-8
U5: NC(CH340X); MSOP10
U6: NC(TJA1050); SOP8
Y1: 8M; 28
Y2: 32.768k; FC-135

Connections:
3V3: C1.1, C2.1, C3.2, C4.2, C13.1, C16.2, C17.2, C18.2, C21.1, P1.20, P2.2, P5.4, P9.1, P9.2, P10.2, P10.4, R1.2, R2.1, R3.1, R4.2, R7.1, R8.1, R9.1, R10.2, R12.2, R13.2, R15.1, U1.2, U2.8, U3.24, U3.36, U3.48, U4.3, U4.7, U4.8, U5.7, U5.10
5V: C12.1, C24.2, F1.2, P10.6, P10.8, U1.3, U6.3
+5V: C20.2, P8.1, P12.A4, P12.B4, P_HUSB0.1, P_HUSB1.A4, P_HUSB1.B4, P_USB.A4, P_USB.B4, S2.1
BOOT0: P3.3, U3.44
BOOT1: P1.13, P3.4, U3.20
CAN0H: P6.1, R17.1, U6.7
CAN0L: P6.2, R17.2, U6.6
DTR: P3.1, R5.1, U5.6
GND: C1.2, C2.2, C3.1, C4.1, C5.2, C6.2, C7.1, C8.1, C11.1, C12.2, C13.2, C14.2, C15.2, C16.1, C17.1, C18.1, C20.1, C21.2, C24.1, D1.2, P2.14, P5.6, P5.10, P8.5, P9.7, P9.8, P10.1, P10.3, P10.5, P10.7, P12.0, P12.A1, P12.B1, P_HUSB0.4, P_HUSB0.5, P_HUSB0.6, P_HUSB1.0, P_HUSB1.A1, P_HUSB1.B1, P_USB.0, P_USB.A1, P_USB.B1, R5.2, R6.2, R16.1, R20.2, R21.2, R22.2, R23.2, R24.2, R25.2, S1.3, U1.1, U2.1, U2.2, U2.3, U2.4, U2.7, U3.8, U3.23, U3.35, U3.47, U4.4, U5.3, U6.2, Y1.0
IIC_SCL: J5.2, R8.2, U2.6
IIC_SDA: J5.1, R9.2, U2.5
LED1: D2.2, P4.1
LED2: D3.2, P4.2
MCU_RXD: P9.6, U5.8
MCU_TXD: P9.4, U5.9
NRST: C11.2, P2.13, P8.4, R4.1, S1.1, U3.7, U5.4
NetD1_1: D1.1, R1.1
NetD2_1: D2.1, R2.2
NetD3_1: D3.1, R3.2
NetF1_1: F1.1, S2.2
NetP3_2: P3.2, R6.1
NetP5_1: P5.1, R12.1
NetP5_2: P5.2, R13.1, R14.1
NetP5_8: P5.8, R15.2
NetP12_A5: P12.A5, R25.1
NetP12_B5: P12.B5, R24.1
NetP_HUSB1_A5: P_HUSB1.A5, R20.1
NetP_HUSB1_B5: P_HUSB1.B5, R21.1
NetP_USB_A5: P_USB.A5, R22.1
NetP_USB_B5: P_USB.B5, R23.1
NetR10_1: R10.1, R11.1, U4.1
NetR16_2: R16.2, U6.8
PA0: P1.3, U3.10
PA1: P1.4, TK1.1, U3.11
PA2: P1.5, R11.2, TK2.1, U3.12
PA3: P1.6, R14.2, U3.13
PA4: P1.7, U3.14
PA5: P1.8, P5.5, U3.15, U4.6
PA6: P1.9, P5.7, U3.16, U4.2
PA7: P1.10, P5.3, U3.17, U4.5
PA8: P2.20, P5.9, U3.29
PA9: P2.19, P9.3, U3.30
PA10: P2.18, P9.5, U3.31
PA11: P2.17, P_USB.A7, P_USB.B7, U3.32
PA12: P2.16, P_USB.A6, P_USB.B6, U3.33
PA13: P2.15, P8.2, U3.34
PA14: P2.12, P8.3, U3.37
PA15: P2.11, U3.38
PB0: P1.11, U3.18
PB1: P1.12, U3.19
PB3: P2.10, U3.39
PB4: P2.9, U3.40
PB5: P2.8, U3.41
PB6: P2.7, P_HUSB0.2, P_HUSB1.A7, P_HUSB1.B7, U3.42
PB7: P2.6, P_HUSB0.3, P_HUSB1.A6, P_HUSB1.B6, U3.43
PB8: P2.5, U3.45, U6.4
PB9: P2.3, U3.46, U6.1
PB10: P1.14, U3.21
PB11: P1.15, U3.22
PB12: P1.16, U3.25
PB13: P1.17, U3.26
PB14: P1.18, U3.27
PB15: P1.19, U3.28
PC13: P2.4, U3.2
PC14: C5.1, U3.3, Y2.1
PC15: C6.1, U3.4, Y2.2
PD0: C7.2, P1.1, U3.5, Y1.2
PD1: C8.2, P1.2, U3.6, Y1.1
UD+: P12.A6, P12.B6, U5.1
UD-: P12.A7, P12.B7, U5.2
VBAT: C14.1, P2.1, U3.1
VDDA: C15.1, R7.2, U3.9

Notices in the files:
EVT/EXAM/ADC/DualADC_Combined_RegInjectionSimul/User/main.c:
Copyright (c) 2021 Nanjing Qinheng Microelectronics Co., Ltd.
